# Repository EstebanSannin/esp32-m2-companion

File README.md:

# esp32-m2-companion

M.2 Key-B 2242 card with an ESP32-S3-WROOM-1 acting as a USB companion MCU
for embedded Linux hosts. Spec: [SPEC.md](SPEC.md) (contract; v2 = amendment A3).

**This branch (`v2`): v2.0 Rev A, in design.** v2 is a feature revision: it adds 12 expansion
lines on the M.2 edge for carrier boards (switched off on every normal host), input
over-voltage protection, and moves to 6 layers. Layout is done (GATE V3 approved); the fab
package is ready but **paused** until the Rev B boards are back. See [v2 status](#status--v20-rev-a-branch-v2).
The ordered board is **v1.0 Rev B** (branch `rev-b`; summary [below](#previous-revision--v10-rev-b)).

<p align="center"><sub>
  Generated render of the v2.0 Rev A board · <a href="docs/img/board_top.png">top</a> ·
  <a href="docs/img/board_bottom.png">bottom</a> (silk logo) · regenerate with <code>make render</code>
</sub></p>

**[→ Product datasheet](DATASHEET.md)** — features, specs, pinout, recovery interface.
**[→ Carrier interface](docs/carrier-interface.md)** — the contract for carrier and accessory boards (v2).
**[→ Layer stackup & routing](docs/stackup.md)** — 6-layer stack (v2), impedance, per-layer copper views.
**[→ Interactive 3D viewer](https://estebansannin.github.io/esp32-m2-companion/3d/viewer.html)**
(GitHub Pages; or download [docs/3d/viewer.html](docs/3d/viewer.html) — fully
offline, GLB embedded) · [STEP](docs/3d/esp32_m2_companion.step) /
[GLB](docs/3d/esp32_m2_companion.glb) for MCAD · regenerate with `make 3d`.

**Open source hardware** — © 2026 Stefano Viola, licensed under
[CERN-OHL-P v2](LICENSE). Designed by Stefano Viola with Claude (Anthropic);
schematic-as-code in SKiDL, all outputs generated (see *Build targets*). The vendored M.2 card-edge footprint derives from
[timonsku/M.2-Card-Footprints](https://github.com/timonsku/M.2-Card-Footprints)
(CERN-OHL-P v2).

## Status — v2.0 Rev A (branch v2)

| Gate | What | State |
|---|---|---|
| V0 | SPEC amendment A3, ADR 0006–0008, [carrier contract](docs/carrier-interface.md) | approved 2026-10-07 |
| V1 | [pinmap, values, ID EEPROM, BOM](docs/v2-gate-v1.md) | approved 2026-10-07 |
| V2 | [schematic](docs/v2-gate-v2.md) (`make check` + pin-by-pin contract check) | approved 2026-10-07 |
| V3 | [layout](docs/v2-gate-v3.md): `make drc` 0 violations / 0 unconnected | approved 2026-10-10 |
| V4 | [fab package](docs/v2-gate-v4.md): `make fab` ready, cost check done | **paused**: JLC placement-preview check of the polarized parts still to do; waiting for the Rev B boards |

What v2 adds (no change for existing hosts):
- **12 expansion lines (EXP_0..11) on otherwise-unused M.2 pins.** They go to ESP32 GPIOs through
  3× TI TMUX1511 switches and stay high-Z unless a carrier grounds CONFIG_2 + CONFIG_3 (the carrier
  signature). EXP_0/1 carry I²C with a carrier ID EEPROM. Contract:
  [docs/carrier-interface.md](docs/carrier-interface.md).
- **Host sidebands:** WWAN LED#, WAKE#, W_DISABLE2# through NMOS cells.
- **Input protection:** TI TPS259470A eFuse on the M.2 3.3 V (≈ 1 A limit, over-voltage cut-off
  3.44–3.57 V).
- **PCB:** 6 layers (JLC06081H-2116), small vias 0.35/0.2; same 2242 size, same module position.
- **Cost:** ≈ $48/board for 5 prototypes, ≈ $11/board at 100 (`docs/v2-gate-v4.md`).

v2 review artifacts: [docs/review/](docs/review/) (`v2_reva_*`: per-block connection tables,
schematic, drawings, BOM, label inventory) · findings log:
[docs/review-findings.md](docs/review-findings.md).

## Previous revision — v1.0 Rev B

Ordered at JLC (W2026100715339652); the board files live on branch `rev-b`.
v1.0 was fabbed, assembled and brought up: every subsystem works on real
hardware ([docs/bringup.md](docs/bringup.md)). Rev B fixes the v1 defects found
there — nothing new functionally:

| v1.0 defect | Rev B fix |
|---|---|
| D3/D4 LEDs assembled 180° reversed (dark) | JLC CPL rotation +180°; `make fab` blocks the order until each polarized part is verified against JLC's preview; silk cathode bar added |
| Green LED under-driven | R3 330 Ω → 100 Ω |
| USB D− via milled away in the B-key notch (needed a jumper) | vias moved out of the notch ([before/after](docs/img/revb_notch_corner.png)) |
| Plated mounting notch → $38 castellation fee | routed notch in the outline: not plated, no copper, no drill |
| USBLC6 and EN-RC capacitor grounds floating | dedicated GND vias |
| DRC waiver hid the notch problem | edge-clearance waiver scoped to the finger pads; `make drc` gate |

Also restored: the M.2 pin-8 (W_DISABLE1#) BOOT leg. Review record: GATE B1
(layout), B2 (labels) approved; ordered 2026-10. Rev B review artifacts:
`docs/review/rev_b_*` · findings log: [docs/review-findings.md](docs/review-findings.md).

## Build targets

| Target | Output |
|---|---|
| `make check` | ERC + netlist + BOM + v2 contract netlist check (after every schematic-source change) |
| `make drc` | DRC gate — fails on any non-excluded violation or unconnected item |
| `make sch` | generated KiCad schematic + PDF |
| `make drawings` | assembly + fab drawings PDF (`docs/review/`) |
| `make labels` | label inventory (`docs/review/`) |
| `uv --directory hardware run python tools/gen_connections.py` | per-block connection tables (`docs/review/v2_reva_connections.md`) |
| `make fab` | JLCPCB gerbers/BOM/CPL + polarity checklist (`fab/`); exit 2 = order blocked |
| `make datasheet` | DATASHEET.md |
| `make render` / `make views` / `make layers` / `make 3d` | renders, labelled views, per-layer views (6 L), GLB/STEP/viewer |

## Host compatibility

| Host | Status |
|---|---|
| Toradex Mallow (Verdin) M.2 Key-B slot | Primary target — **validated on hardware** (v1.0 bring-up on Verdin iMX8MP, docs/bringup.md) |
| Raspberry Pi 5 + Waveshare "PCIe TO 4G/5G M.2 USB3.2 HAT+" | Nice-to-have (ADR 0004) — HAT officially fits 3042/3052 (2242 standoff TBD), sideband wiring unpublished |
| Raspberry Pi official M.2 HAT+ | **NOT compatible** — M-key, PCIe only, no USB on the socket |
| Companion carrier boards (v2) | EXP bus enabled by the carrier signature; first one: dev carrier (separate repo `m2-dev-carrier`) |

Note: the card is taller than the M.2 single-sided envelope (module 3.1 mm,
JST plug ≈ 6.3 mm on the top side vs 1.5 mm) — fine in open slots like Mallow's,
not for enclosed hosts (risks R11).

## Layout

- `docs/datasheets/` — all reference documents (provenance in its README)
- `docs/pinmap.md` — M.2 edge + ESP32-S3 pin allocation (GATE 1; v2 in §6)
- `docs/carrier-interface.md` — v2 card ↔ carrier contract
- `docs/v2-gate-v*.md` — v2 gate packages (V1–V4)
- `docs/decisions/` — ADRs
- `docs/risks.md` — risk register
- `docs/bringup.md` — v1.0 bring-up log + Rev B checks
- `docs/review/` — review artifacts (`v2_reva_*` for v2, `rev_b_*` kept as history)
- `fab/README.md` — JLCPCB order settings (v2, 6 L) + polarity-preview procedure
- `v2/` — research and history behind v2 (brainstorm, part research, routing probe)
- `docs/environment.md` — tool install log
- `hardware/` — schematic-as-code + KiCad (Phase 1+)
- `firmware/` — ESP-IDF project (Phase 4)

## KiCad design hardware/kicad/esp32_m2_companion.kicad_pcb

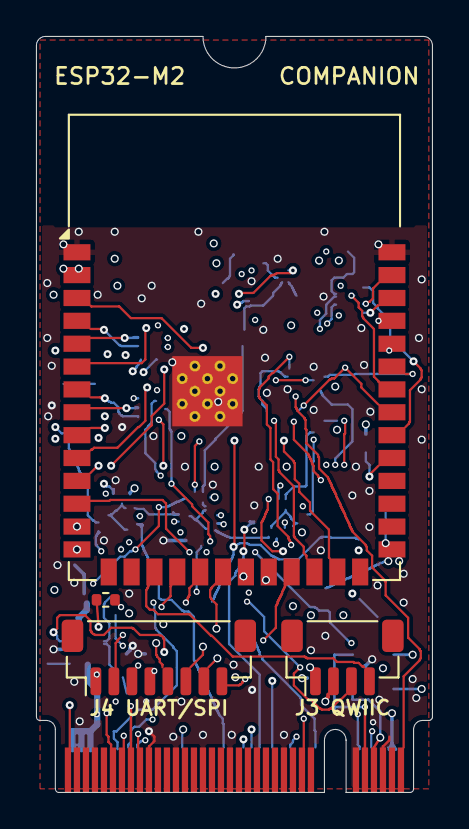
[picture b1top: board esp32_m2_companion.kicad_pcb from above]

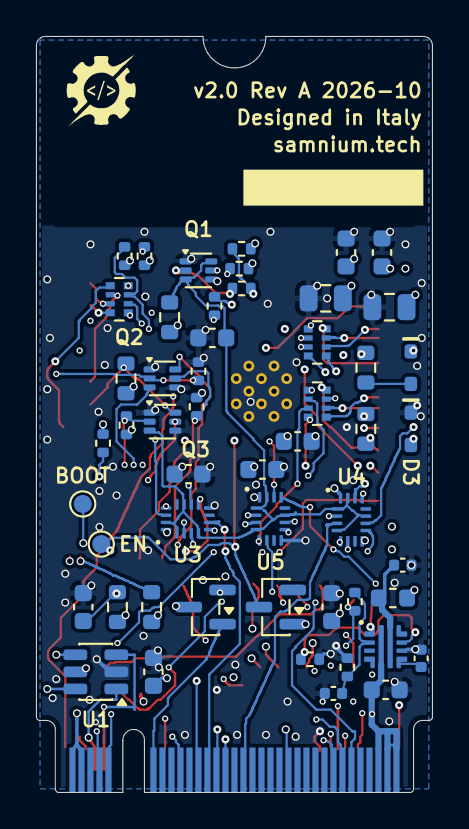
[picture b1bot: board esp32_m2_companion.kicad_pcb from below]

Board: 6 copper layers, 22.0 x 42.0 mm, 57 parts (52 on the bottom side), 78 nets.

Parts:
C1, C2: 22uF 25V; C_0805_2012Metric
C3, C7: 10uF 10V; C_0603_1608Metric
C4, C6, C10, C11, C12, C14: 100nF 50V; C_0603_1608Metric
C5, C13: 1uF 50V; C_0603_1608Metric
C15: 2.2nF 50V; C_0402_1005Metric
C16: 100pF C0G; C_0402_1005Metric
C17: 1uF 25V; C_0402_1005Metric
D1, D2: BAT54A; SOT-23
D3: green; LED_TJ-S1706_SideView
D4: red; LED_TJ-S1706_SideView
FB1: 120R@100MHz 2A; L_0603_1608Metric
J1: M2_KEYB_2242_EDGE; M2_KeyB_2242_EdgeFingers
J3: Conn_01x04; JST_SH_BM04B-SRSS-TB_1x04-1MP_P1.00mm_Vertical
J4: Conn_01x08; JST_SH_BM08B-SRSS-TB_1x08-1MP_P1.00mm_Vertical
Q1, Q2, Q3: SSM6N56FE; SOT-563
R1, R2, R26, R30: 10k; R_0603_1608Metric
R3: 100R; R_0603_1608Metric
R4: 330R; R_0603_1608Metric
R20, R21: 4k7; R_0402_1005Metric
R22, R23, R33: 1M; R_0402_1005Metric
R24, R25, R27, R28, R29, R35: 100k; R_0402_1005Metric
R31: 100k 0.1%; R_0402_1005Metric
R32: 52.3k 0.1%; R_0402_1005Metric
R34: 3.3k; R_0402_1005Metric
RN1, RN2, RN3: 220R; R_Array_Convex_4x0402
TP1: TP_EN; TestPoint_Pad_D1.0mm
TP2: TP_BOOT; TestPoint_Pad_D1.0mm
U1: USBLC6-2SC6; SOT-23-6
U2: ESP32-S3-WROOM-1; ESP32-S3-WROOM-1_JLC
U3, U4, U5: TMUX1511_RSV; TI_RSV0016A_UQFN-16_1.8x2.6mm_P0.4mm
U6: TPS259470A_RPW; TI_RPW_VQFN-10_2x2mm_P0.5mm

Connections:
+3V3: C1.1, C2.1, C3.1, C4.1, C6.1, C7.1, C10.1, C11.1, C12.1, FB1.2, J3.2, R1.1, R2.1, R3.1, R4.1, R20.1, R21.1, R22.1, R23.1, R26.1, R29.1, R30.1, R35.1, U1.5, U2.2, U3.16, U4.16, U5.16
+3V3_EFUSE: C17.1, FB1.1, U6.6
+3V3_M2: C14.1, J1.2, J1.4, J1.70, J1.72, J1.74, R31.1, R33.1, U6.5
CFG2_G: Q1.2, R24.2
CFG3_G: Q1.5, R25.2
CONFIG_2: J1.75, R22.2, R24.1
CONFIG_3: J1.1, R23.2, R25.1
EFUSE_DVDT: C15.1, U6.7
EFUSE_EN: R33.2, U6.1
EFUSE_ILM: R34.1, U6.9
EFUSE_OVLO: C16.1, R31.2, R32.1, U6.2
EN: C5.1, D1.3, R1.2, TP1.1, U2.3
EXP_0: J1.30, U3.3
EXP_0_S: R20.2, RN1.8, U3.2
EXP_1: J1.32, U3.6
EXP_1_S: R21.2, RN1.7, U3.5
EXP_2: J1.34, U3.9
EXP_2_S: RN1.6, U3.10
EXP_3: J1.36, U3.13
EXP_3_S: RN1.5, U3.14
EXP_4: J1.40, U4.3
EXP_4_S: RN2.8, U4.2
EXP_5: J1.59, U4.6
EXP_5_S: RN2.7, U4.5
EXP_6: J1.60, U4.9
EXP_6_S: RN2.6, U4.10
EXP_7: J1.61, U4.13
EXP_7_S: RN2.5, U4.14
EXP_8: J1.62, U5.3
EXP_8_S: RN3.8, U5.2
EXP_9: J1.63, U5.6
EXP_9_S: RN3.7, U5.5
EXP_10: J1.64, U5.9
EXP_10_S: RN3.6, U5.10
EXP_11: J1.65, U5.13
EXP_11_S: RN3.5, U5.14
EXP_OE: C13.1, Q1.3, Q1.6, Q3.3, R26.2, U3.1, U3.4, U3.11, U3.15, U4.1, U4.4, U4.11, U4.15, U5.1, U5.4, U5.11, U5.15
GND: C1.2, C2.2, C3.2, C4.2, C5.2, C6.2, C7.2, C10.2, C11.2, C12.2, C13.2, C14.2, C15.2, C16.2, C17.2, D3.1, J1.3, J1.5, J1.11, J1.21, J1.27, J1.33, J1.39, J1.45, J1.51, J1.57, J1.69, J1.71, J1.73, J3.1, Q1.1, Q1.4, Q2.1, Q2.4, Q3.1, Q3.4, R27.2, R28.2, R32.2, R34.2, U1.2, U2.1, U2.40, U2.41, U3.8, U4.8, U5.8, U6.8
IO0: D2.3, R2.2, TP2.1, U2.27
IO1: RN1.3, U2.39
IO2: RN1.4, U2.38
IO4: RN2.2, U2.4
IO5: RN2.3, U2.5
IO6: RN2.4, U2.6
IO7: RN3.1, U2.7
IO8: J3.3, U2.12
IO9: J3.4, U2.17
IO10: J4.3, U2.18
IO11: J4.4, U2.19
IO12: J4.5, U2.20
IO13: J4.6, U2.21
IO14: J4.7, U2.22
IO15: RN3.2, U2.8
IO16: RN3.3, U2.9
IO17: RN3.4, U2.10
IO18: RN2.1, U2.11
IO21: J4.8, U2.23
IO38: Q3.5, R35.2, U2.31
IO39: RN1.1, U2.32
IO40: Q3.6, R30.2, U2.33
IO41: RN1.2, U2.34
IO42: Q2.2, R27.1, U2.35
IO47: Q2.5, R28.1, U2.24
LED_1_n: J1.10, Q2.6
LED_PWR_A: D3.2, R3.2
LED_STATUS_A: D4.2, R4.2
LED_STATUS_n: D4.1, U2.25
PCIE_1_GPIO_5: D2.1, J1.20
PERST_n: D1.1, J1.50
RXD0: J4.2, U2.36
TXD0: J4.1, U2.37
USBH3_D_N: J1.9, U1.3
USBH3_D_P: J1.7, U1.1
USB_D_N: U1.4, U2.13
USB_D_P: U1.6, U2.14
WAKE_ON_WWAN_n: J1.23, Q2.3
W_DISABLE1_n: D2.2, J1.8
W_DISABLE2_n: J1.26, Q3.2, R29.2

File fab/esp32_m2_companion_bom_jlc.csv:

Comment,Designator,Footprint,LCSC Part #
22uF 25V,"C1,C2",C_0805_2012Metric,C45783
100nF 50V,"C10,C11,C12,C14,C4,C6",C_0603_1608Metric,C14663
1uF 50V,"C13,C5",C_0603_1608Metric,C15849
2.2nF 50V,C15,C_0402_1005Metric,C1531
100pF C0G,C16,C_0402_1005Metric,C1546
1uF 25V,C17,C_0402_1005Metric,C52923
10uF 10V,"C3,C7",C_0603_1608Metric,C19702
BAT54A,"D1,D2",SOT-23,C12743
green,D3,LED_TJ-S1706_SideView,C273616
red,D4,LED_TJ-S1706_SideView,C273612
120R@100MHz 2A,FB1,L_0603_1608Metric,C14709
Conn_01x04,J3,JST_SH_BM04B-SRSS-TB_1x04-1MP_P1.00mm_Vertical,C160390
Conn_01x08,J4,JST_SH_BM08B-SRSS-TB_1x08-1MP_P1.00mm_Vertical,C160394
SSM6N56FE,"Q1,Q2,Q3",SOT-563,C146449
10k,"R1,R2,R26,R30",R_0603_1608Metric,C25804
4k7,"R20,R21",R_0402_1005Metric,C25900
1M,"R22,R23,R33",R_0402_1005Metric,C26083
100k,"R24,R25,R27,R28,R29,R35",R_0402_1005Metric,C25741
100R,R3,R_0603_1608Metric,C22775
100k 0.1%,R31,R_0402_1005Metric,C852472
52.3k 0.1%,R32,R_0402_1005Metric,C852832
3.3k,R34,R_0402_1005Metric,C25890
330R,R4,R_0603_1608Metric,C23138
220R,"RN1,RN2,RN3",R_Array_Convex_4x0402,C25498
USBLC6-2SC6,U1,SOT-23-6,C7519
ESP32-S3-WROOM-1,U2,ESP32-S3-WROOM-1_JLC,C2913204
TMUX1511_RSV,"U3,U4,U5",TI_RSV0016A_UQFN-16_1.8x2.6mm_P0.4mm,C2673275
TPS259470A_RPW,U6,TI_RPW_VQFN-10_2x2mm_P0.5mm,C3662799

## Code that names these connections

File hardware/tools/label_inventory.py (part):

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NET_SOURCE = {
    "GND": "power", "+3V3": "power (card rail, after FB1)",
    "+3V3_M2": "power (M.2 3.3 V input, before FB1)",
    "USBH3_D_P": "Mallow X17 (M.2 pin 7)", "USBH3_D_N": "Mallow X17 (M.2 pin 9)",
    "PERST_n": "Mallow X17 PERST# (M.2 pin 50), # -> _n",
    "PCIE_1_GPIO_5": "Mallow X17 (M.2 pin 20)",
    "W_DISABLE1_n": "M.2 WWAN W_DISABLE1# (pin 8), # -> _n",
    "EN": "WROOM-1 pin name", "TXD0": "WROOM-1 pin name", "RXD0": "WROOM-1 pin name",
    "USB_D_N": "WROOM-1 pin name (IO19/USB_D-)", "USB_D_P": "WROOM-1 pin name (IO20/USB_D+)",
    "USB_D_N_ESD": "derived: USB_D_N between U1 and series R8",
    "USB_D_P_ESD": "derived: USB_D_P between U1 and series R7",
    "LED_STATUS_n": "functional (IO48, active-low LED cathode)",
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
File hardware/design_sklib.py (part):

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
design = SchLib(tool=SKIDL).add_parts(*[
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            Pin(num='1',name='CONFIG_3',func=pin_types.INPUT),
            Pin(num='2',name='VCC_3V3',func=pin_types.PWRIN),
            Pin(num='3',name='GND',func=pin_types.PWRIN),
            Pin(num='4',name='VCC_3V3',func=pin_types.PWRIN),
            Pin(num='5',name='GND',func=pin_types.PWRIN),
            Pin(num='6',name='FULL_CARD_POWER_OFF_n',func=pin_types.NOCONNECT),
            Pin(num='7',name='USBH3_D_P',func=pin_types.BIDIR),
            Pin(num='8',name='W_DISABLE1_n',func=pin_types.INPUT),
            Pin(num='9',name='USBH3_D_N',func=pin_types.BIDIR),
            Pin(num='10',name='WWAN_LED_n',func=pin_types.PASSIVE),
            Pin(num='11',name='GND',func=pin_types.PWRIN),
            Pin(num='20',name='PCIE_1_GPIO_5',func=pin_types.INPUT),
            Pin(num='21',name='CONFIG_0',func=pin_types.PASSIVE),
            Pin(num='22',name='PCIE_1_GPIO_6',func=pin_types.NOCONNECT),
            Pin(num='23',name='PCIE_1_GPIO_11',func=pin_types.PASSIVE),
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            Pin(num='47',name='PCIE_1_L0_TX_N',func=pin_types.NOCONNECT),
            Pin(num='48',name='PCIE_1_GPIO_4',func=pin_types.NOCONNECT),
            Pin(num='49',name='PCIE_1_L0_TX_P',func=pin_types.NOCONNECT),
            Pin(num='50',name='PERST_n',func=pin_types.INPUT),
            Pin(num='51',name='GND',func=pin_types.PWRIN),
            Pin(num='52',name='PCIE_CLKREQ_n',func=pin_types.NOCONNECT),
            Pin(num='53',name='PCIE_1_CLK_N',func=pin_types.NOCONNECT),
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            Pin(num='72',name='VCC_3V3',func=pin_types.PWRIN),
            Pin(num='73',name='GND',func=pin_types.PWRIN),
            Pin(num='74',name='VCC_3V3',func=pin_types.PWRIN),
            Pin(num='75',name='CONFIG_2',func=pin_types.INPUT)] }),
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            Pin(num='1',name='EN_UVLO',func=pin_types.INPUT),
            Pin(num='2',name='OVLO',func=pin_types.INPUT),
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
